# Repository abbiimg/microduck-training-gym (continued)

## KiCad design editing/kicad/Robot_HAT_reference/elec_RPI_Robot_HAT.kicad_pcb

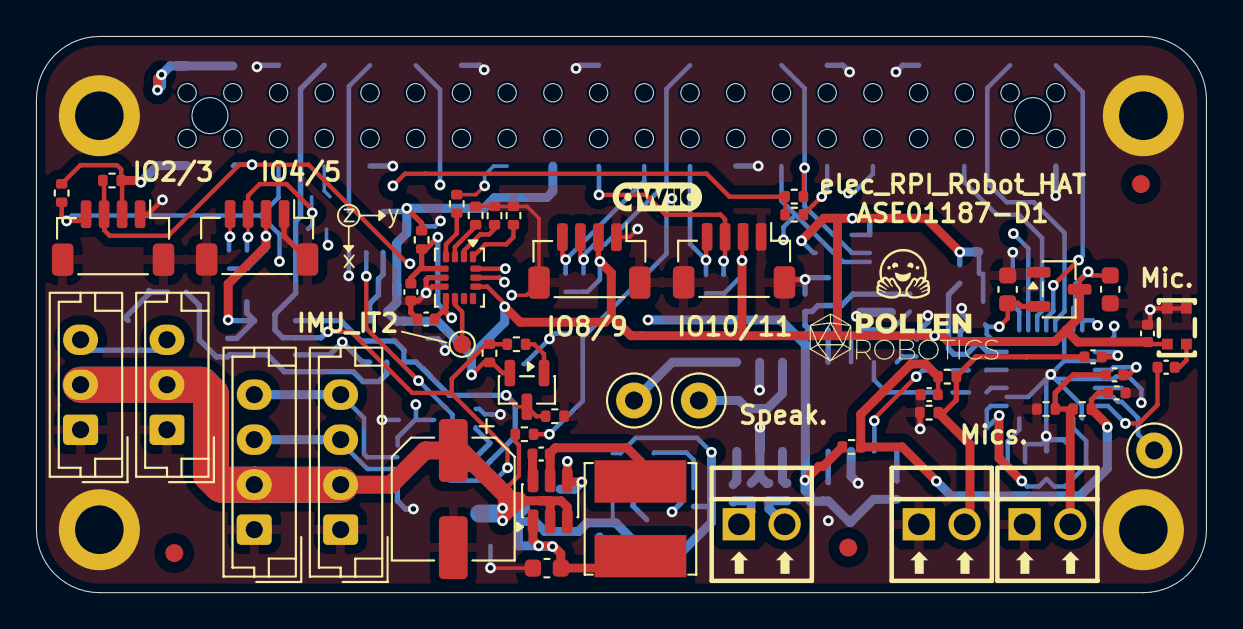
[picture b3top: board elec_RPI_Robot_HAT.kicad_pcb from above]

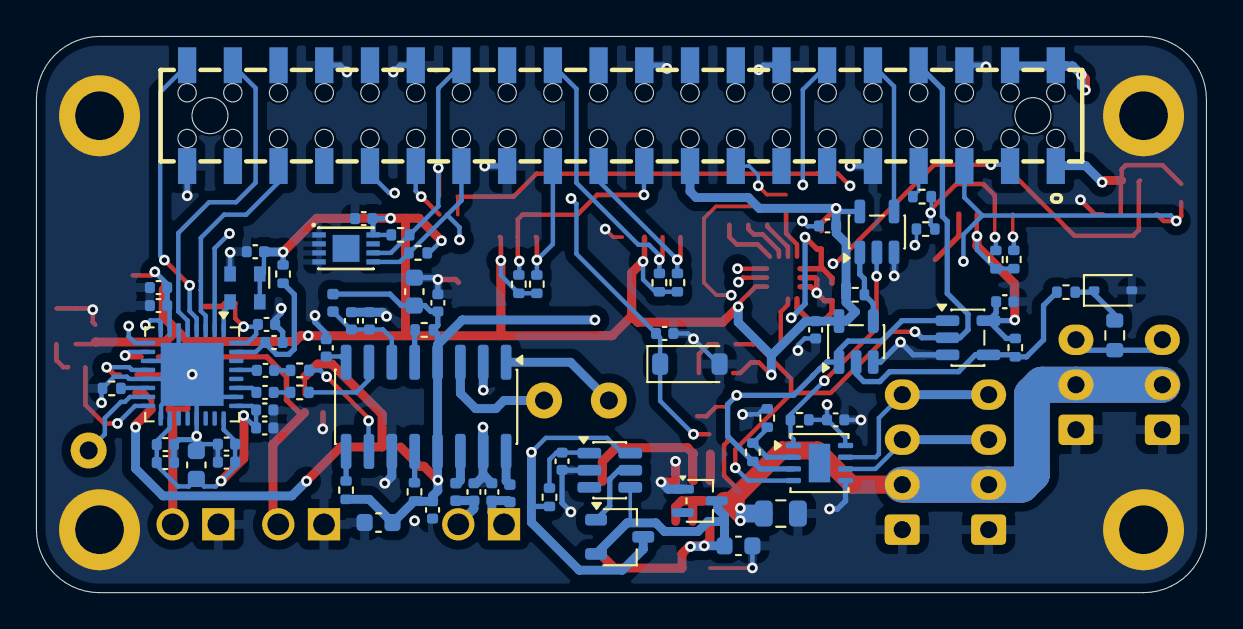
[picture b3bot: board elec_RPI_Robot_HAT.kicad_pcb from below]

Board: 4 copper layers, 65.0 x 30.9 mm, 132 parts (74 on the bottom side), 74 nets.

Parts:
C1, C2, C3, C4, C6, C10, C27, C29, C31, C33, C35, C40, C41, C42, C43: 1u; C_0402_1005Metric
C5, C7, C12, C13, C37: 10u; C_0603_1608Metric
C8, C9: 220n; C_0402_1005Metric
C11, C14, C15, C16, C17, C18, C26, C28, C30, C32, C36, C38: 100n; C_0402_1005Metric
C19: 10u 63V; CP_Elec_6.3x7.7
C20: 100n 50V; C_0402_1005Metric
C21, C22: 22u 6V3; C_0603_1608Metric
C23, C24, C39: 100n 6V3; C_0402_1005Metric
C25: DNP-100n; C_0402_1005Metric
C34, C44: 10n; C_0402_1005Metric
C45: 10u 35V; C_0805_2012Metric
D1: BAT54W; SOT-323_SC-70
D2: 3V3 Zener Diode; D_SOD-123
D4: 5V1; D_SOD-323
FB1: 1.3A 600R@100MHz; L_0402_1005Metric
FB2, FB3: 2A - 120R@100MHz; L_0402_1005Metric
FID1, FID2, FID3: DNP Fiducial; Fiducial_1mm_Mask2mm
G1: qwiic_Logo; Logo_qwiic_5mm
H2: Logo HF 2025; Logo_HF_2025
H3: DNP Logo Pollen 2021; Logo_Pollen_2021_sq
J1, J2, J9: Screw term.; CONN-TH_DB125-2.54-2P-GN
J3, J11: Dynamixel-4; JST_EH_B4B-EH-A_1x04_P2.50mm_Vertical
J4: Female Header 2x20 SMD; PinHeader_2x20_P2.54mm_Vertical_with_rasp_HAT_zero_SMD_conn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
J5, J6, J7, J8: JST SH; JST_SH_BM04B-SRSS-TB_1x04-1MP_P1.00mm_Vertical
J13, J14: Dynamixel-3; JST_EH_B3B-EH-A_1x03_P2.50mm_Vertical
L4: 6,8u 2A; L_Bourns_SRN6045TA
MK1: Microphone_MEMS; MIC-SMD_4P-L2.8-W1.9-P1.84-TL
Q1: MMBT3906; SOT-23
Q2: N-Channel 5A; TSOT-23
R1, R2, R6, R12, R13, R20, R21, R24, R26, R27, R29, R31, R32, R34, R35, R38, R39: 10k; R_0402_1005Metric
R3, R4, R5, R7, R9, R14, R15, R18, R19, R25, R30, R40: 0R; R_0402_1005Metric
R8: 100R; R_0402_1005Metric
R10, R11: DNP-10k; R_0402_1005Metric
R16, R17, R41: DNP-0R; R_0402_1005Metric
R22, R23: 4k7; R_0402_1005Metric
R28: 20k; R_0402_1005Metric
R33: 150R; R_0402_1005Metric
R36, R37: DNP-1M; R_0402_1005Metric
R42: 1k; R_0402_1005Metric
TH1: 100R thermistor; R_0603_1608Metric
TP2, TP3, TP4: TestPoint; TestPoint_Loop_D2.50mm_Drill1.0mm_LowProfile
TP5: TestPoint; TestPoint_Pad_D1.0mm
U1: PAM8406D; SOIC-16_3.9x9.9mm_P1.27mm
U2: TLV320AIC3104IRHBR; VQFN-32-1EP_5x5mm_P0.5mm_EP3.5x3.5mm
U3: XC6206P182MR; SOT-23-3
U4: DNP-CAT24C32HU4; TDFN-8_L3.0-W2.0-P0.50-BL-EP
U5: 74LVC1G08; SOT-23-5
U6: SN74LVC1G125DBV; SOT-23-5
U7: SN74LVC1G126DBVR; SOT-23-5
U8: GM3088ENA; DFN-8-1EP_3x3mm_P0.65mm_EP1.2x2.15mm
U9: AP63205; TSOT-23-6
U10: LM5050-1; TSOT-23-6
U12: LSM6DSV16XTR; LGA-14_3x2.5mm_P0.5mm_LayoutBorder3x4y
Y1: 12 MHz; Oscillator_SMD_Abracon_ASDMB-4Pin_2.5x2.0mm

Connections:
+1V8: C12.1, C26.2, U2.32 (DVDD), U3.2 (VO)
+3V3: C11.2, C13.1, C14.2, C15.2, C16.2, C17.2, C18.2, C25.2, C27.2, C28.2, C29.2, C30.2, C31.2, C32.2, C35.2, C36.2, C37.1, J4.1, J4.17, J5.2, J6.2, J7.2, J8.2, MK1.4 (+), Q1.2 (E), R6.1, R9.2, R10.1, R11.1, R12.1, R13.1, R20.1, R21.1, R26.2, R29.1, R31.1, R32.1, R34.1, R35.1, R38.1, R39.1, U2.7 (IOVDD), U2.18 (DRVDD), U2.24 (DRVDD), U2.25 (AVDD), U3.3 (VI), U4.8 (VCC), U5.5 (VCC), U6.5 (VCC), U7.5 (VCC), U8.8 (VCC), U12.12 (CS), Y1.1 (Tri-State), Y1.4 (VDD)
+5V: C4.1, C5.1, C6.1, C7.1, FB1.2, J4.2, J4.4, Q2.3 (D), R3.2, R4.2, R5.2, R8.1, R42.1, U1.4 (PVDDL), U1.13 (PVDDR), U10.6 (OUT)
+BATT: C19.1, C45.1, J3.2, J11.2, J13.2, J14.2, R24.2, U9.2 (EN), U9.3 (IN)
/Schematic/Audio/ID_SC: J4.28, R10.2, R16.1, U4.6 (SCL)
/Schematic/Audio/ID_SD: J4.27, R11.2, R17.1, U4.5 (SDA)
/Schematic/Audio/IO_02: J4.3, J5.3, R12.2, U2.9 (SDA), U12.14 (SDA)
/Schematic/Audio/IO_03: J4.5, J5.4, R13.2, U2.8 (SCL), U12.13 (SCL)
/Schematic/Audio/IO_04: J4.7, R18.1
/Schematic/Audio/IO_05: J4.29, R19.1
/Schematic/Audio/IO_06: C44.1, D2.1 (K), J4.31, R24.1
/Schematic/Audio/IO_08: J4.24, J7.3, R34.2
/Schematic/Audio/IO_09: J4.21, J7.4, R35.2
/Schematic/Audio/IO_10: J4.19, J8.3, R38.2
/Schematic/Audio/IO_11: J4.23, J8.4, R39.2
/Schematic/Audio/IO_14: J4.8, R26.1, R27.1, U7.2, U8.4 (DI)
/Schematic/Audio/IO_15: J4.10, U5.4
/Schematic/Audio/IO_18: J4.12, U2.2 (BCLK)
/Schematic/Audio/IO_19: J4.35, U2.3 (WCLK)
/Schematic/Audio/IO_20: J4.38, U2.5 (DOUT)
/Schematic/Audio/IO_21: J4.40, U2.4 (DIN)
/Schematic/Audio/IO_22: J4.15, R25.1
/Schematic/Dynamixel/Dynamixel_dir: Q1.3 (C), R28.2, R40.1, U6.1, U7.1, U8.3 (DE)
GND: C3.1, C4.2, C5.2, C6.2, C7.2, C8.2, C9.2, C11.1, C12.2, C13.2, C14.1, C15.1, C16.1, C17.1, C18.1, C19.2, C21.2, C22.2, C23.2, C24.1, C25.1, C26.1, C27.1, C28.1, C29.1, C30.1, C31.1, C32.1, C33.2, C34.2, C35.1, C36.1, C37.2, C38.1, C39.2, C42.1, C43.1, C44.2, C45.2, D1.1 (A), D2.2 (A), D4.2 (A), J2.1, J3.1, J4.6, J4.9, J4.14, J4.20, J4.25, J4.30, J4.34, J4.39, J4.MP (MountPin), J5.1, J5.MP (MountPin), J6.1, J6.MP (MountPin), J7.1, J7.MP (MountPin), J8.1, J8.MP (MountPin), J9.1, J11.1, J13.1, J14.1, MK1.2 (-), MK1.3 (-), R7.1, R14.1, R15.1, R28.1, R30.1, R36.1, R37.1, R41.1, U1.2 (PGNDL), U1.11 (GND), U1.15 (PGNDR), U2.6 (DVSS), U2.11 (MIC1LM/LINE1LM), U2.13 (MIC1RM/LINE1RM), U2.17 (AVSS1), U2.21 (DRVSS), U2.26 (AVSS2), U2.33 (EP), U3.1 (GND), U4.1 (A0), U4.2 (A1), U4.3 (A2), U4.4 (GND), U5.3 (GND), U6.3 (GND), U7.3 (GND), U8.5 (GND), U9.4 (GND), U10.2 (GND), U12.6 (GND), U12.7 (GND), Y1.2 (GND)
unnamed: C1.2, R1.1
unnamed: C2.2, R2.1
unnamed: C10.1, MK1.1 (-)
unnamed: C42.2, C43.2, R22.2, R23.2, R42.2
unnamed: C21.1, C22.1, D1.3 (K), L4.1, Q2.2 (S), U9.1 (FB), U10.4 (IN)
unnamed: D4.1 (K), R33.2, TH1.1
unnamed: C9.1, FB3.2, J1.1
unnamed: C8.1, FB2.2, J1.2
unnamed: C41.2, J2.2, R22.1, R36.2
unnamed: J6.3, R17.2, R18.2, R20.2
unnamed: J6.4, R16.2, R19.2, R21.2
unnamed: C40.2, J9.2, R23.1, R37.2
unnamed: J3.3, J11.3, U8.6 (A)
unnamed: J3.4, J11.4, U8.7 (B)
unnamed: J13.3, J14.3, TH1.2
unnamed: Q1.1 (B), R27.2
unnamed: Q2.1 (G), U10.5 (GATE)
unnamed: R31.2, U5.1, U6.4
unnamed: R32.2, R33.1, U6.2, U7.4
unnamed: TP3.1, U1.1 (+OUT_L)
unnamed: FB3.1, U1.16 (+OUT_R)
unnamed: TP4.1, U1.3 (-OUT_L)
unnamed: FB2.1, U1.14 (-OUT_R)
unnamed: R1.2, U1.7 (INL)
unnamed: R2.2, U1.10 (INR)
unnamed: R5.1, U1.9 (MODE)
unnamed: C33.1, C34.1, FB1.1, U1.6 (VDD)
unnamed: C3.2, U1.8 (VREF)
unnamed: R4.1, U1.5 (~MUTE)
unnamed: R3.1, U1.12 (~SHND)
unnamed: C1.1, U2.27 (LEFT_LOP)
unnamed: U2.1 (MCLK), Y1.3 (OUT)
unnamed: C41.1, U2.10 (MIC1LP/LINE1LP)
unnamed: C40.1, U2.12 (MIC1RP/LINE1RP)
unnamed: R7.2, U2.14 (MIC2L/LINE2L/MICDET)
unnamed: C10.2, U2.16 (MIC2R/LINE2R)
unnamed: TP2.1, U2.15 (MICBIAS)
unnamed: C2.1, U2.29 (RIGHT_LOP)
unnamed: C38.2, R6.2, U2.31 (~RESET)
unnamed: R29.2, U5.2, U8.1 (RO)
unnamed: R40.2, R41.2, U8.2 (~RE)
unnamed: C20.1, U9.6 (BST)
unnamed: C20.2, L4.2, U9.5 (SW)
unnamed: C39.1, R8.2, U10.1 (VS)
unnamed: R25.2, U12.4 (INT1)
unnamed: TP5.1, U12.9 (INT2)
unnamed: R15.2, U12.3 (SCX)
unnamed: R30.2, U12.1 (SDO/SA0)
unnamed: R14.2, U12.2 (SDX)
unnamed: C23.1, C24.2, R9.1, U12.5 (VDDIO), U12.8 (VDD)

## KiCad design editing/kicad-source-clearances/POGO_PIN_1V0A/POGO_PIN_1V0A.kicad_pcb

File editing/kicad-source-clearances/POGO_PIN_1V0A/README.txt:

Bounded source-clearance engineering copy. Copper/board bytes unchanged. Explicit supported SAFE pairs plus conservative zone/edge/drill envelopes; global defaults retained for unmapped objects. Full source-rule fidelity and manufacturing readiness remain false. Read ../../../SOURCE-CLEARANCE-PROGRESS.txt. Never refill static copper.

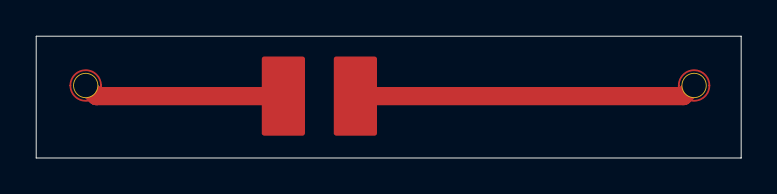
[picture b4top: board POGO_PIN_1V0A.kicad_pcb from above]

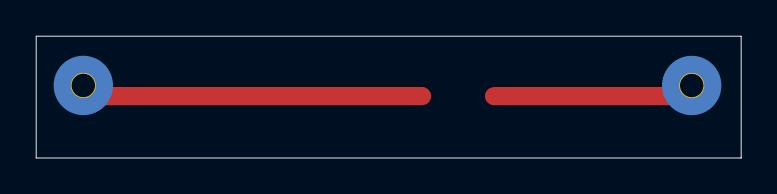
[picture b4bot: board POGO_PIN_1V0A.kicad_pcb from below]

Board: 2 copper layers, 39.2 x 6.8 mm, 3 parts (2 on the bottom side), 2 nets.

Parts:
SOURCE_BOARD_PADS: (no value)
U1: YZ39730097P-01; U1
U2: YZ39730097P-01; U2

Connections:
/Battery: SOURCE_BOARD_PADS.2, U1.1
/GND: SOURCE_BOARD_PADS.1, U2.1

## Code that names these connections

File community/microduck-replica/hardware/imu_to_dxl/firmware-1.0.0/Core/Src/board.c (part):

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    GPIOB->BSRR = 1UL << BOARD_RX_EN_PIN; /* receiver ON */
    pin_mode(GPIOA, 1u, 1u);
    pin_mode(GPIOA, 4u, 1u);
    pin_mode(GPIOB, 8u, 3u); /* tied PB8 pad must never fight PB7 */
    pin_mode(GPIOB, BOARD_RX_EN_PIN, 1u);
    clock_init();
    RCC->APBENR1 |= RCC_APBENR1_TIM2EN | RCC_APBENR1_USART2EN;
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    TIM2->CR1 = TIM_CR1_CEN;
    (void)SysTick_Config(SystemCoreClock / 1000u);
    NVIC_SetPriority(SysTick_IRQn, 2u);
    /* SPI1 AF0: PA5=SCK, PA6=MISO, PA7=MOSI. */
    pin_af(GPIOA, 5u, 0u); pin_af(GPIOA, 6u, 0u); pin_af(GPIOA, 7u, 0u);
    spi_init();
    /* USART2 AF1, external single-wire buffers: do NOT set UART HDSEL. */
    GPIOA->PUPDR = (GPIOA->PUPDR & ~(3UL << 6)) | (1UL << 6); /* PA3 pull-up */
    pin_af(GPIOA, 2u, 1u); pin_af(GPIOA, 3u, 1u);
    USART2->CR1 = 0;
    USART2->BRR = (SystemCoreClock + BOARD_BUS_BAUD / 2u) / BOARD_BUS_BAUD;
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    USART2->ICR = USART_ICR_ORECF | USART_ICR_FECF | USART_ICR_NECF | USART_ICR_PECF;
    USART2->CR1 = USART_CR1_UE | USART_CR1_TE | USART_CR1_RE | USART_CR1_RXNEIE_RXFNEIE;
    NVIC_SetPriority(USART2_IRQn, 0u); NVIC_EnableIRQ(USART2_IRQn);
    /* TSSOP20 package pins 16/17: route PA9/10 onto PA11/12 pads. */
    SYSCFG->CFGR1 |= SYSCFG_CFGR1_PA11_RMP | SYSCFG_CFGR1_PA12_RMP;
    pin_af(GPIOA, 9u, 1u); pin_af(GPIOA, 10u, 1u);
    USART1->CR1 = 0;
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        ++board_diagnostics.tx_busy_drops;
        NVIC_EnableIRQ(USART2_IRQn); unlock_irq(irq); return -2;
    }
    GPIOB->BRR = 1UL << BOARD_RX_EN_PIN; /* suppress local echo; PA3 pull-up stays on */
    USART2->ICR = USART_ICR_TCCF;
    GPIOA->BRR = 1UL << 1; /* 1OE# LOW -> drive bus */
    unlock_irq(irq);
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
